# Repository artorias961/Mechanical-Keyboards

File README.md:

# Summary

This project documents the design and iteration of custom mechanical keyboards, covering schematic capture and PCB layout in KiCad, along with firmware and key-mapping experiments. The repository tracks multiple hardware revisions, including an archived AVR-based design and a newer ESP32-S3 implementation exploring wireless connectivity, expanded I/O, and modern MCU capabilities.

The goal is to serve as both a personal learning record and a practical reference for others interested in building custom keyboards from the ground up.

## Lore / Why this exists

Pretty much I’m a keyboard fanatic — I’ve owned ~5 keyboards. During COVID I spent most of my time at home and wanted to learn PCB design. My first version was a huge learning curve, so I’m keeping everything here so others can use it as a reference (or improve it beyond what I could do)

## Keyboard versions

### Version 2 — ESP32-S3-WROOM-1

**Why ESP32-S3:**
- The main seller is **Bluetooth** + **serial pins**.
- ESP32-S3-WROOM-1 is positioned as a flagship ESP chip.
- More computing power, memory, and I/O flexibility than ATMEGA32A-PU 

(You also captured a quick MCU comparison table in the repo notes.) 

| Feature / MCU             | ATmega328P                                 | ATmega32A-PU                | Raspberry Pi Pico (RP2040)                    | ESP32 (e.g., Nano ESP32)                              |
| ------------------------- | ------------------------------------------ | --------------------------- | --------------------------------------------- | ----------------------------------------------------- |
| **Architecture**          | 8-bit AVR                                  | 8-bit AVR                   | 32-bit ARM Cortex-M0+                         | 32-bit Tensilica Xtensa (some variants up to 240 MHz) |
| **Clock Speed**           | ~20 MHz typical                            | ~16 MHz typical             | 133 MHz dual-core                             | Up to ~240 MHz dual-core                              |
| **Flash Memory**          | 32 KB                                      | 32 KB                       | 2 MB (on board)                               | 4 MB+ typical                                         |
| **SRAM**                  | ~2 KB                                      | ~2 KB                       | ~264 KB                                       | ~520 KB+                                              |
| **I/O Pins**              | ~23 I/O                                    | ~32 I/O                     | ~26 GPIO                                      | ~30+ GPIO                                             |
| **Wireless Connectivity** | None                                       | None                        | Default none (Pico); **Pico W has Wi-Fi/BLE** | Wi-Fi & Bluetooth built-in                            |
| **USB Support**           | Needs external interface                   | Needs external interface    | USB device (native)                           | USB & Serial                                          |
| **Power**                 | Low                                        | Low                         | Moderate                                      | Moderate                                              |
| **Ease of Programming**   | Arduino IDE / Atmel Studio                 | Arduino IDE / Atmel Studio  | C/C++, MicroPython                            | Arduino IDE, MicroPython, FreeRTOS                    |
| **Typical Use**           | Simple control, low power, classic Arduino | Similar to 328 with more IO | Faster MCU tasks, multicore                   | IoT, wireless, rich features                          |
| **Price (chip only)**     | ~$2–$3                                     | ~$4–$6                      | ~$3–$6                                        | ~$10–$20                                              |

### Version 1 — ATMEGA32A-PU (Archive)

**Why ATMEGA32A-PU (vs ATMEGA328):**
- Preferred over ATMEGA328 due to **more pins**.
- No dedicated serial pins.
- Enough pins for **LEDs**, an **OLED**, and possibly a Bluetooth module.
- Main concern: **not wireless**.

This version wasn’t manufactured at the time due to a ~$100 quote for a single PCB (around 2021). Here are some pictures from V1:

## Key footprint sizing notes

Standard keyboard size footprints captured in the repo notes: 
- Majority are **1.0U**
- **Seven** 1.25U
- **Two** 1.50U
- **One** 1.75U
- **One** 2.00U
- **Two** 2.25U
- **One** 2.75U
- **One** 6.25U

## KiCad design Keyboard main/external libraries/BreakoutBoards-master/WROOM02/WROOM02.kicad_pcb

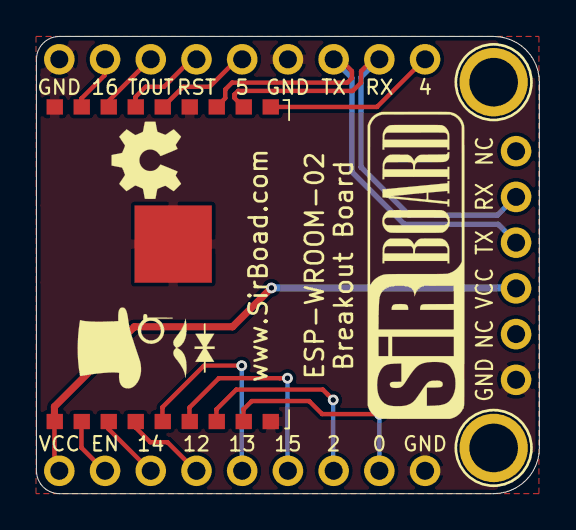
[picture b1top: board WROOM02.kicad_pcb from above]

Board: 2 copper layers, 27.9 x 25.4 mm, 6 parts (0 on the bottom side), 16 nets.

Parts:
H1, H2: MountingHole; MountingHole_M2.5_SirBoard
J1, J2: Conn_01x09; PinHeader_1x09_P2.54mm_Vertical
J3: Conn_01x06; PinHeader_1x06_P2.54mm_Vertical
U1: ESP-WROOM-02

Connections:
EN: J1.2, U1.2
GND: J1.9, J2.1, J2.6, J3.1, U1.9, U1.13, U1.18, U1.19
GPI16: J2.2, U1.17
GPIO0: J1.8, U1.8
GPIO2: J1.7, U1.7
GPIO4: J2.9, U1.10
GPIO5: J2.5, U1.14
GPIO12: J1.4, U1.4
GPIO13: J1.5, U1.5
GPIO14: J1.3, U1.3
GPIO15: J1.6, U1.6
RST: J2.4, U1.15
RXD: J2.8, J3.5, U1.11
TOUT: J2.3, U1.16
TXD: J2.7, J3.4, U1.12
VCC: J1.1, J3.3, U1.1

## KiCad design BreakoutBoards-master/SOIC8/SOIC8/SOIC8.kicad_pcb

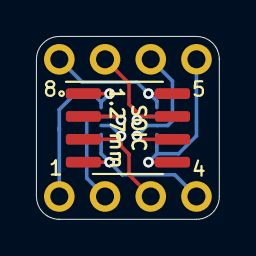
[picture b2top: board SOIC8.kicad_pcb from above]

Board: 2 copper layers, 10.2 x 10.2 mm, 4 parts (1 on the bottom side), 8 nets.

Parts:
J1, J2: Conn_01x04; PinHeader_1x04_P2.54mm_Vertical
J3: SOIC8; SOIC-8_3.9x4.9mm_P1.27mm
J4: VSSOP8; VSSOP-8_2.3x2mm_P0.5mm

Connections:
unnamed: J1.1, J3.8, J4.1
unnamed: J1.2, J3.7, J4.2
unnamed: J1.3, J3.6, J4.3
unnamed: J1.4, J3.5, J4.4
unnamed: J2.1, J3.1, J4.8
unnamed: J2.2, J3.2, J4.7
unnamed: J2.3, J3.3, J4.6
unnamed: J2.4, J3.4, J4.5

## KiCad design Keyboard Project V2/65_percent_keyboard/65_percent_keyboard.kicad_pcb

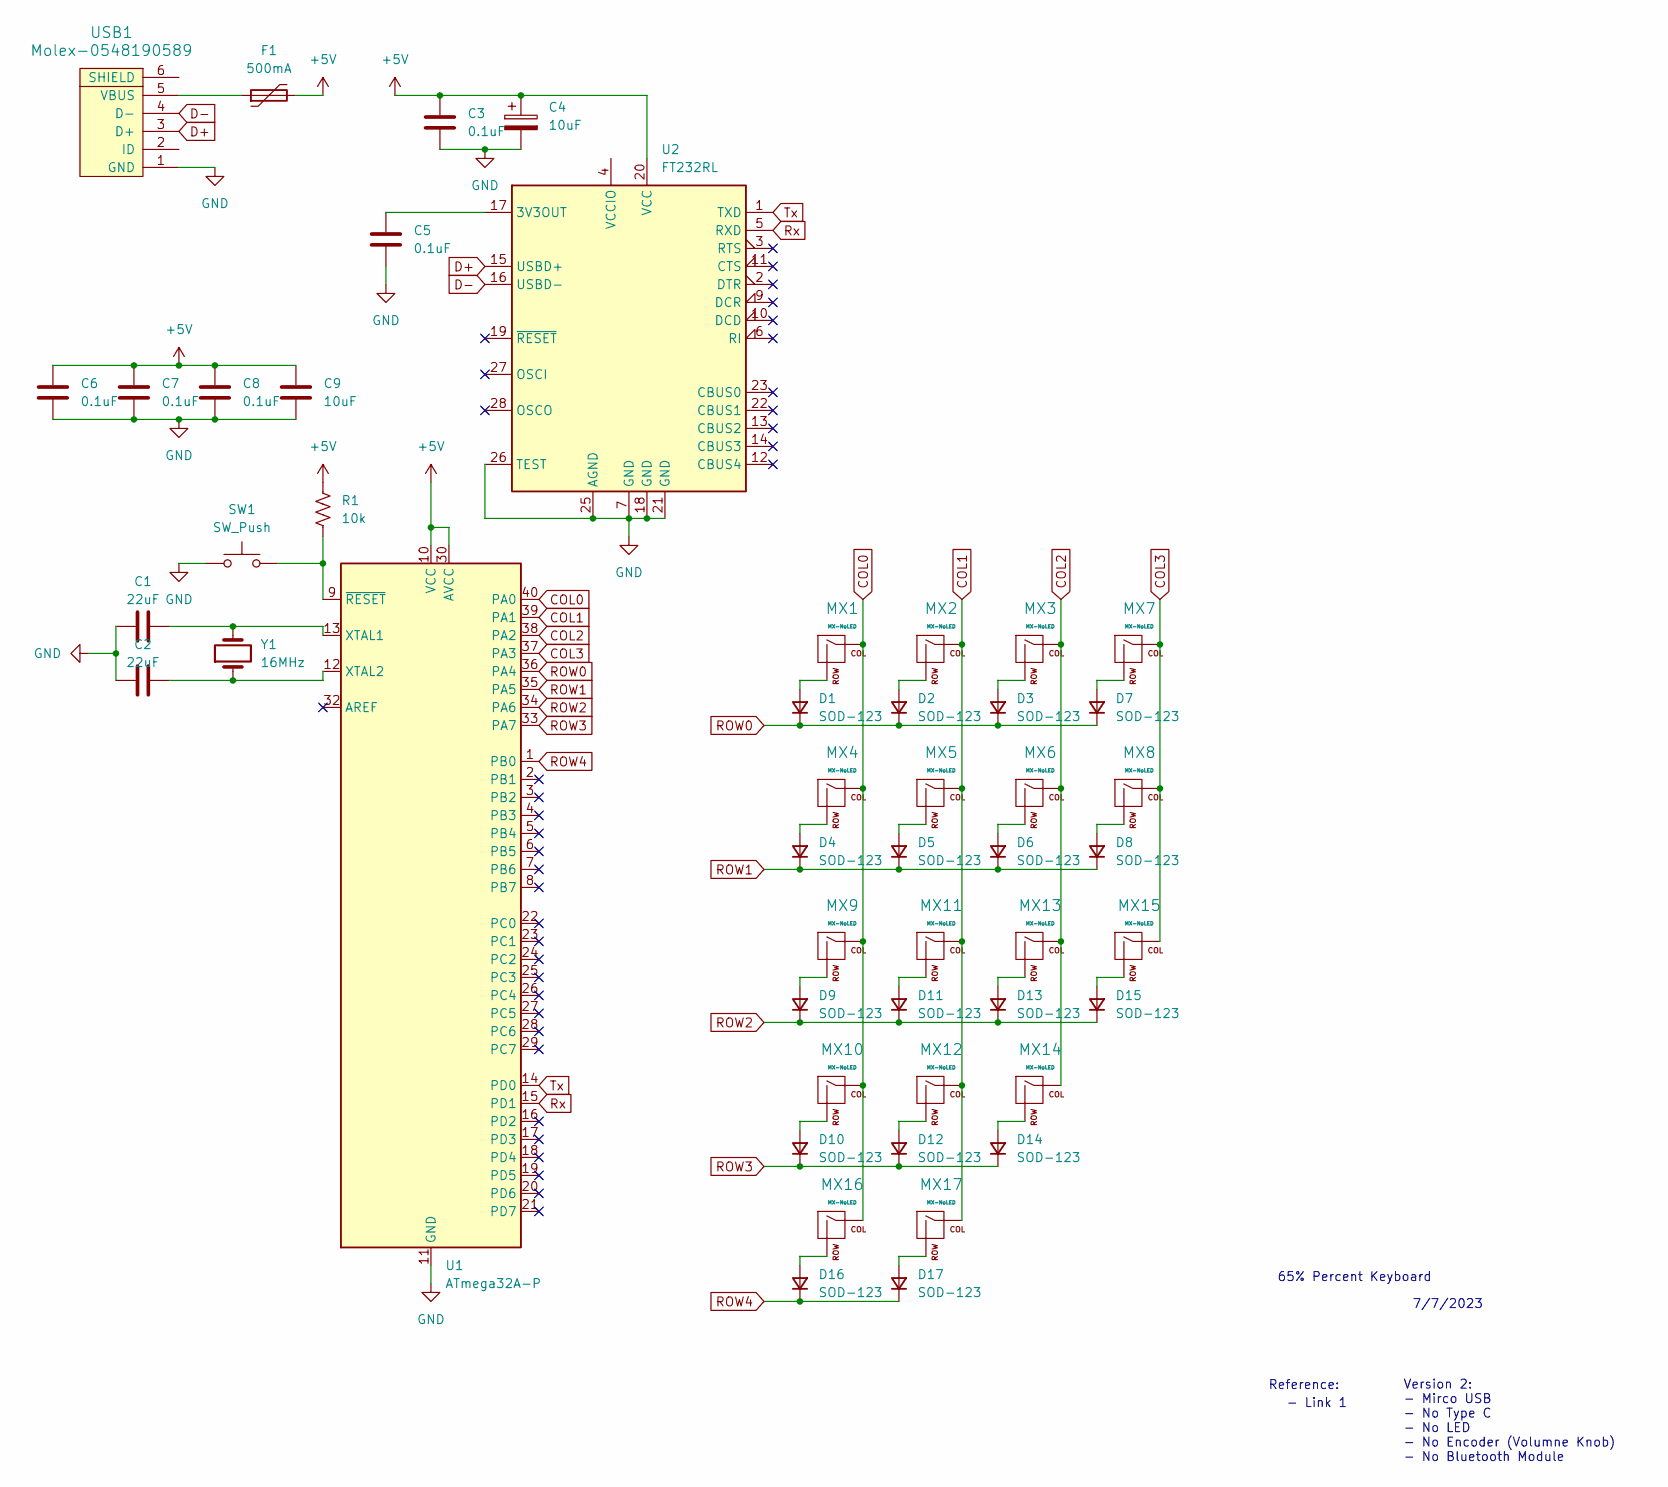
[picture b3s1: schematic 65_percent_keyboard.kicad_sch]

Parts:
C1, C2: 22uF; C_0805_2012Metric
C3, C5, C6, C7, C8: 0.1uF; C_0805_2012Metric
C4, C9: 10uF; C_0805_2012Metric
D1, D2, D3, D4, D5, D6, D7, D8, D9, D10, D11, D12, D13, D14, D15, D16, D17: SOD-123; D_SOD-123
F1: 500mA; Fuse_1206_3216Metric
MX1, MX2, MX3, MX4, MX5, MX6, MX7, MX8, MX9, MX10, MX11, MX12, MX13, MX14, MX15, MX16, MX17: MX-NoLED; MX-1U-NoLED
R1: 10k; R_0805_2012Metric
SW1: SW_Push; SKQG-1155865
U1: ATmega32A-P; DIP-40_W15.24mm
U2: FT232RL; SSOP-28_5.3x10.2mm_P0.65mm
USB1: Molex-0548190589
Y1: 16MHz; Crystal_SMD_3225-4Pin_3.2x2.5mm

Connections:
+5V: C3.1, C4.1, C6.1, C7.1, C8.1, C9.1, F1.2, R1.2, U1.10 (VCC), U1.30 (AVCC), U2.20 (VCC)
COL0: MX1.1 (COL), MX4.1 (COL), MX9.1 (COL), MX10.1 (COL), MX16.1 (COL), U1.40 (PA0)
COL1: MX2.1 (COL), MX5.1 (COL), MX11.1 (COL), MX12.1 (COL), MX17.1 (COL), U1.39 (PA1)
COL2: MX3.1 (COL), MX6.1 (COL), MX13.1 (COL), MX14.1 (COL), U1.38 (PA2)
COL3: MX7.1 (COL), MX8.1 (COL), MX15.1 (COL), U1.37 (PA3)
D+: U2.15 (USBD+), USB1.3 (D+)
D-: U2.16 (USBD-), USB1.4 (D-)
GND: C1.1, C2.1, C3.2, C4.2, C5.2, C6.2, C7.2, C8.2, C9.2, SW1.1, U1.11 (GND), U1.31 (GND), U2.7 (GND), U2.18 (GND), U2.21 (GND), U2.25 (AGND), U2.26 (TEST), USB1.1 (GND)
unnamed: D1.2 (A), MX1.2 (ROW)
unnamed: D2.2 (A), MX2.2 (ROW)
unnamed: D3.2 (A), MX3.2 (ROW)
unnamed: D4.2 (A), MX4.2 (ROW)
unnamed: D5.2 (A), MX5.2 (ROW)
unnamed: D6.2 (A), MX6.2 (ROW)
unnamed: D7.2 (A), MX7.2 (ROW)
unnamed: D8.2 (A), MX8.2 (ROW)
unnamed: D9.2 (A), MX9.2 (ROW)
unnamed: D10.2 (A), MX10.2 (ROW)
unnamed: D11.2 (A), MX11.2 (ROW)
unnamed: D12.2 (A), MX12.2 (ROW)
unnamed: D13.2 (A), MX13.2 (ROW)
unnamed: D14.2 (A), MX14.2 (ROW)
unnamed: D15.2 (A), MX15.2 (ROW)
unnamed: D16.2 (A), MX16.2 (ROW)
unnamed: D17.2 (A), MX17.2 (ROW)
unnamed: C1.2, U1.13 (XTAL1), Y1.2
unnamed: C2.2, U1.12 (XTAL2), Y1.1
unnamed: R1.1, SW1.2, U1.9 (~RESET)
unnamed: C5.1, U2.17 (3V3OUT)
unnamed: F1.1, USB1.5 (VBUS)
ROW0: D1.1 (K), D2.1 (K), D3.1 (K), D7.1 (K), U1.36 (PA4)
ROW1: D4.1 (K), D5.1 (K), D6.1 (K), D8.1 (K), U1.35 (PA5)
ROW2: D9.1 (K), D11.1 (K), D13.1 (K), D15.1 (K), U1.34 (PA6)
ROW3: D10.1 (K), D12.1 (K), D14.1 (K), U1.33 (PA7)
ROW4: D16.1 (K), D17.1 (K), U1.1 (PB0)
Rx: U1.15 (PD1), U2.5 (RXD)
Tx: U1.14 (PD0), U2.1 (TXD)

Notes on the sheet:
Version 2: - Mirco USB - No Type C - No LED - No Encoder (Volumne Knob) - No Bluetooth Module
65% Percent Keyboard
7/7/2023
- Link 1
Reference:

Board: 2 copper layers, 50 parts (0 on the bottom side), 37 nets, no tracks yet.

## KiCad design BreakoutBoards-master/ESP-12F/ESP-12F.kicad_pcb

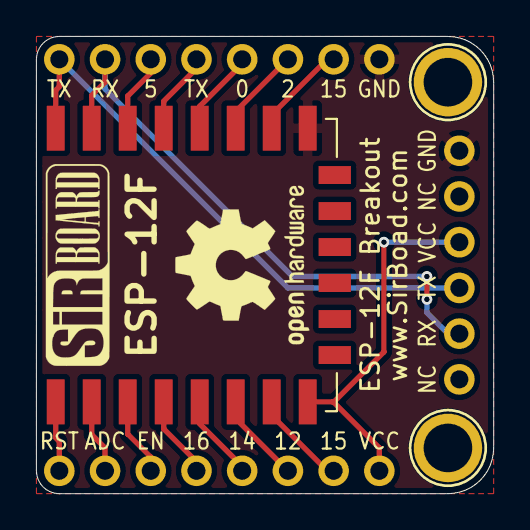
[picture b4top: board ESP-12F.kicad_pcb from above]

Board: 2 copper layers, 25.4 x 25.4 mm, 6 parts (0 on the bottom side), 16 nets.

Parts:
ESP-12F: ESP-12F; ESP-12E
H2, H4: MountingHole; MountingHole_M2.5_SirBoard
J1, J2: Conn_01x08; PinHeader_1x08_P2.54mm_Vertical
J3: Conn_01x06; PinHeader_1x06_P2.54mm_Horizontal

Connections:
ADC: ESP-12F.2, J1.2
EN: ESP-12F.3, J1.3
GND: ESP-12F.15, J2.8, J3.1
GPI16: ESP-12F.4, J1.4
GPIO0: ESP-12F.18, J2.5
GPIO2: ESP-12F.17, J2.6
GPIO4: ESP-12F.19, J2.4
GPIO5: ESP-12F.20, J2.3
GPIO12: ESP-12F.6, J1.6
GPIO13: ESP-12F.7, J1.7
GPIO14: ESP-12F.5, J1.5
GPIO15: ESP-12F.16, J2.7
RST: ESP-12F.1, J1.1
RX: ESP-12F.21, J2.2, J3.5
TXD: ESP-12F.22, J2.1, J3.4
VCC: ESP-12F.8, J1.8, J3.3

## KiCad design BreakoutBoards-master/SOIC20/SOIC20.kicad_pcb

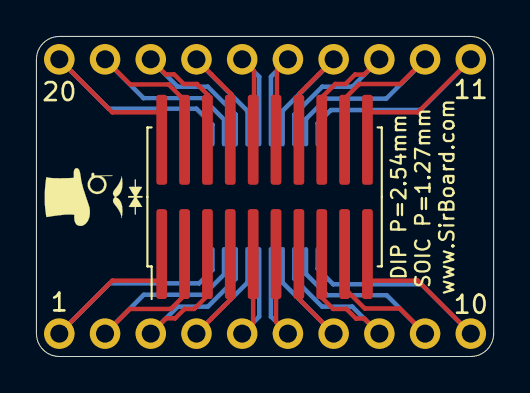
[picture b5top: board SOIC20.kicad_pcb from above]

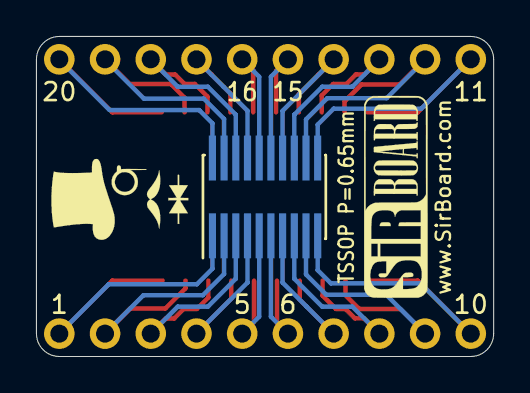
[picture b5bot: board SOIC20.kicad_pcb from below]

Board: 2 copper layers, 25.4 x 17.8 mm, 4 parts (3 on the bottom side), 20 nets.

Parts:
J1, J5: Conn_01x10; PinHeader_1x10_P2.54mm_Vertical
J2: Conn_02x10_Counter_Clockwise; SOIC-20W_7.5x12.8mm_P1.27mm
J4: Conn_02x10_Counter_Clockwise; SSOP-20_4.4x6.5mm_P0.65mm

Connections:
unnamed: J1.1, J2.1, J4.10
unnamed: J1.2, J2.2, J4.9
unnamed: J1.3, J2.3, J4.8
unnamed: J1.4, J2.4, J4.7
unnamed: J1.5, J2.5, J4.6
unnamed: J1.6, J2.6, J4.5
unnamed: J1.7, J2.7, J4.4
unnamed: J1.8, J2.8, J4.3
unnamed: J1.9, J2.9, J4.2
unnamed: J1.10, J2.10, J4.1
unnamed: J2.11, J4.20, J5.1
unnamed: J2.12, J4.19, J5.2
unnamed: J2.13, J4.18, J5.3
unnamed: J2.14, J4.17, J5.4
unnamed: J2.15, J4.16, J5.5
unnamed: J2.16, J4.15, J5.6
unnamed: J2.17, J4.14, J5.7
unnamed: J2.18, J4.13, J5.8
unnamed: J2.19, J4.12, J5.9
unnamed: J2.20, J4.11, J5.10

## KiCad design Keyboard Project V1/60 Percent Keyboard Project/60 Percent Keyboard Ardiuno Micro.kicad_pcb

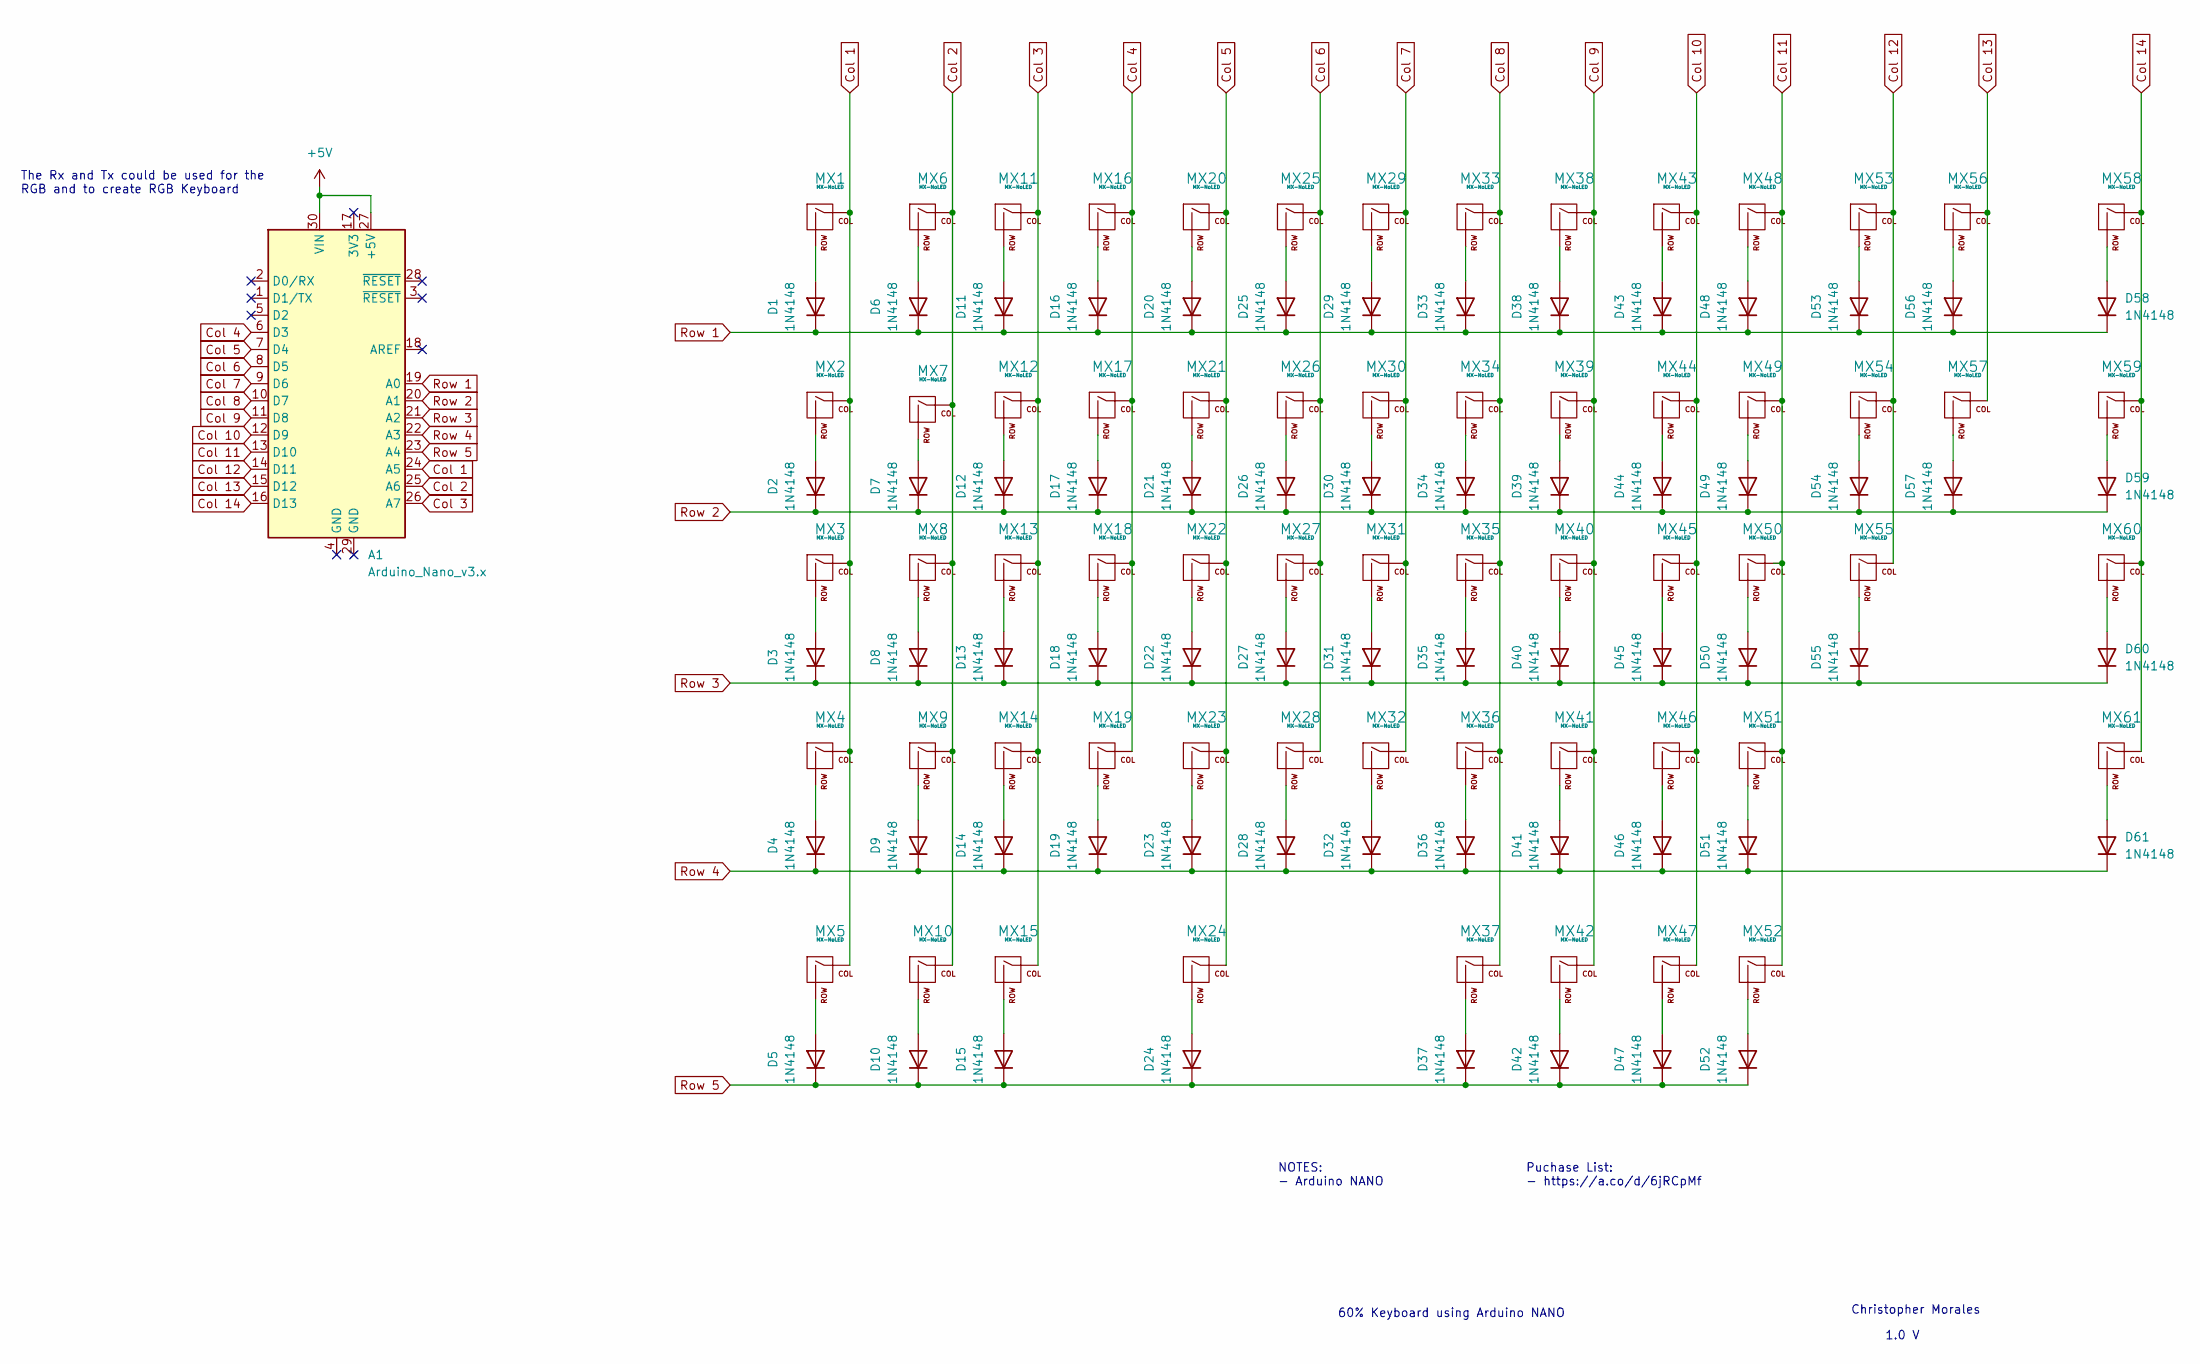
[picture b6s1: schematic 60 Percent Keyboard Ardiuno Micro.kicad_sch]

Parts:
A1: Arduino_Nano_v3.x; Arduino_Nano
D1, D2, D3, D4, D5, D6, D7, D8, D9, D10, D11, D12, D13, D14, D15, D16, D17, D18, D19, D20, D21, D22, D23, D24, D25, D26, D27, D28, D29, D30, D31, D32, D33, D34, D35, D36, D37, D38, D39, D40, D41, D42, D43, D44, D45, D46, D47, D48, D49, D50, D51, D52, D53, D54, D55, D56, D57, D58, D59, D60, D61: 1N4148; D_DO-35_SOD27_P7.62mm_Horizontal
MX1, MX6, MX7, MX8, MX9, MX11, MX12, MX13, MX14, MX16, MX17, MX18, MX19, MX20, MX21, MX22, MX23, MX25, MX26, MX27, MX28, MX29, MX30, MX31, MX32, MX33, MX34, MX35, MX36, MX38, MX39, MX40, MX41, MX43, MX44, MX45, MX46, MX48, MX49, MX50, MX51, MX53, MX54, MX55, MX56, MX57: MX-NoLED; SW_Cherry_MX_PCB_1.00u
MX2, MX59: MX-NoLED; SW_Cherry_MX_PCB_1.50u
MX3: MX-NoLED; SW_Cherry_MX_PCB_1.75u
MX4, MX60: MX-NoLED; SW_Cherry_MX_PCB_2.25u
MX5, MX10, MX15, MX37, MX42, MX47, MX52: MX-NoLED; SW_Cherry_MX_PCB_1.25u
MX24: MX-NoLED; SW_Cherry_MX_PCB_6.25u
MX58: MX-NoLED; SW_Cherry_MX_PCB_2.00u
MX61: MX-NoLED; SW_Cherry_MX_PCB_2.75u

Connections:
Col 1: A1.24 (A5), MX1.1 (COL), MX2.1 (COL), MX3.1 (COL), MX4.1 (COL), MX5.1 (COL)
Col 2: A1.25 (A6), MX6.1 (COL), MX7.1 (COL), MX8.1 (COL), MX9.1 (COL), MX10.1 (COL)
Col 3: A1.26 (A7), MX11.1 (COL), MX12.1 (COL), MX13.1 (COL), MX14.1 (COL), MX15.1 (COL)
Col 4: A1.6 (D3), MX16.1 (COL), MX17.1 (COL), MX18.1 (COL), MX19.1 (COL)
Col 5: A1.7 (D4), MX20.1 (COL), MX21.1 (COL), MX22.1 (COL), MX23.1 (COL), MX24.1 (COL)
Col 6: A1.8 (D5), MX25.1 (COL), MX26.1 (COL), MX27.1 (COL), MX28.1 (COL)
Col 7: A1.9 (D6), MX29.1 (COL), MX30.1 (COL), MX31.1 (COL), MX32.1 (COL)
Col 8: A1.10 (D7), MX33.1 (COL), MX34.1 (COL), MX35.1 (COL), MX36.1 (COL), MX37.1 (COL)
Col 9: A1.11 (D8), MX38.1 (COL), MX39.1 (COL), MX40.1 (COL), MX41.1 (COL), MX42.1 (COL)
Col 10: A1.12 (D9), MX43.1 (COL), MX44.1 (COL), MX45.1 (COL), MX46.1 (COL), MX47.1 (COL)
Col 11: A1.13 (D10), MX48.1 (COL), MX49.1 (COL), MX50.1 (COL), MX51.1 (COL), MX52.1 (COL)
Col 12: A1.14 (D11), MX53.1 (COL), MX54.1 (COL), MX55.1 (COL)
Col 13: A1.15 (D12), MX56.1 (COL), MX57.1 (COL)
Col 14: A1.16 (D13), MX58.1 (COL), MX59.1 (COL), MX60.1 (COL), MX61.1 (COL)
unnamed: D1.2 (A), MX1.2 (ROW)
unnamed: D2.2 (A), MX2.2 (ROW)
unnamed: D3.2 (A), MX3.2 (ROW)
unnamed: D4.2 (A), MX4.2 (ROW)
unnamed: D5.2 (A), MX5.2 (ROW)
unnamed: D6.2 (A), MX6.2 (ROW)
unnamed: D7.2 (A), MX7.2 (ROW)
unnamed: D8.2 (A), MX8.2 (ROW)
unnamed: D9.2 (A), MX9.2 (ROW)
unnamed: D10.2 (A), MX10.2 (ROW)
unnamed: D11.2 (A), MX11.2 (ROW)
unnamed: D12.2 (A), MX12.2 (ROW)
unnamed: D13.2 (A), MX13.2 (ROW)
unnamed: D14.2 (A), MX14.2 (ROW)
unnamed: D15.2 (A), MX15.2 (ROW)
unnamed: D16.2 (A), MX16.2 (ROW)
unnamed: D17.2 (A), MX17.2 (ROW)
unnamed: D18.2 (A), MX18.2 (ROW)
unnamed: D19.2 (A), MX19.2 (ROW)
unnamed: D20.2 (A), MX20.2 (ROW)
unnamed: D21.2 (A), MX21.2 (ROW)
unnamed: D22.2 (A), MX22.2 (ROW)
unnamed: D23.2 (A), MX23.2 (ROW)
unnamed: D24.2 (A), MX24.2 (ROW)
unnamed: D25.2 (A), MX25.2 (ROW)
unnamed: D26.2 (A), MX26.2 (ROW)
unnamed: D27.2 (A), MX27.2 (ROW)
unnamed: D28.2 (A), MX28.2 (ROW)
unnamed: D29.2 (A), MX29.2 (ROW)
unnamed: D30.2 (A), MX30.2 (ROW)
unnamed: D31.2 (A), MX31.2 (ROW)
unnamed: D32.2 (A), MX32.2 (ROW)
unnamed: D33.2 (A), MX33.2 (ROW)
unnamed: D34.2 (A), MX34.2 (ROW)
unnamed: D35.2 (A), MX35.2 (ROW)
unnamed: D36.2 (A), MX36.2 (ROW)
unnamed: D37.2 (A), MX37.2 (ROW)
unnamed: D38.2 (A), MX38.2 (ROW)
unnamed: D39.2 (A), MX39.2 (ROW)
unnamed: D40.2 (A), MX40.2 (ROW)
unnamed: D41.2 (A), MX41.2 (ROW)
unnamed: D42.2 (A), MX42.2 (ROW)
unnamed: D43.2 (A), MX43.2 (ROW)
unnamed: D44.2 (A), MX44.2 (ROW)
unnamed: D45.2 (A), MX45.2 (ROW)
unnamed: D46.2 (A), MX46.2 (ROW)
unnamed: D47.2 (A), MX47.2 (ROW)
unnamed: D48.2 (A), MX48.2 (ROW)
unnamed: D49.2 (A), MX49.2 (ROW)
unnamed: D50.2 (A), MX50.2 (ROW)
unnamed: D51.2 (A), MX51.2 (ROW)
unnamed: D52.2 (A), MX52.2 (ROW)
unnamed: D53.2 (A), MX53.2 (ROW)
unnamed: D54.2 (A), MX54.2 (ROW)
unnamed: D55.2 (A), MX55.2 (ROW)
unnamed: D56.2 (A), MX56.2 (ROW)
unnamed: D57.2 (A), MX57.2 (ROW)
unnamed: D58.2 (A), MX58.2 (ROW)
unnamed: D59.2 (A), MX59.2 (ROW)
unnamed: D60.2 (A), MX60.2 (ROW)
unnamed: D61.2 (A), MX61.2 (ROW)
Row 1: A1.19 (A0), D1.1 (K), D6.1 (K), D11.1 (K), D16.1 (K), D20.1 (K), D25.1 (K), D29.1 (K), D33.1 (K), D38.1 (K), D43.1 (K), D48.1 (K), D53.1 (K), D56.1 (K), D58.1 (K)
Row 2: A1.20 (A1), D2.1 (K), D7.1 (K), D12.1 (K), D17.1 (K), D21.1 (K), D26.1 (K), D30.1 (K), D34.1 (K), D39.1 (K), D44.1 (K), D49.1 (K), D54.1 (K), D57.1 (K), D59.1 (K)
Row 3: A1.21 (A2), D3.1 (K), D8.1 (K), D13.1 (K), D18.1 (K), D22.1 (K), D27.1 (K), D31.1 (K), D35.1 (K), D40.1 (K), D45.1 (K), D50.1 (K), D55.1 (K), D60.1 (K)
Row 4: A1.22 (A3), D4.1 (K), D9.1 (K), D14.1 (K), D19.1 (K), D23.1 (K), D28.1 (K), D32.1 (K), D36.1 (K), D41.1 (K), D46.1 (K), D51.1 (K), D61.1 (K)
Row 5: A1.23 (A4), D5.1 (K), D10.1 (K), D15.1 (K), D24.1 (K), D37.1 (K), D42.1 (K), D47.1 (K), D52.1 (K)

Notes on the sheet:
1.0 V
The Rx and Tx could be used for the RGB and to create RGB Keyboard
Puchase List: - https://a.co/d/6jRCpMf
Christopher Morales
60% Keyboard using Arduino NANO
NOTES: - Arduino NANO

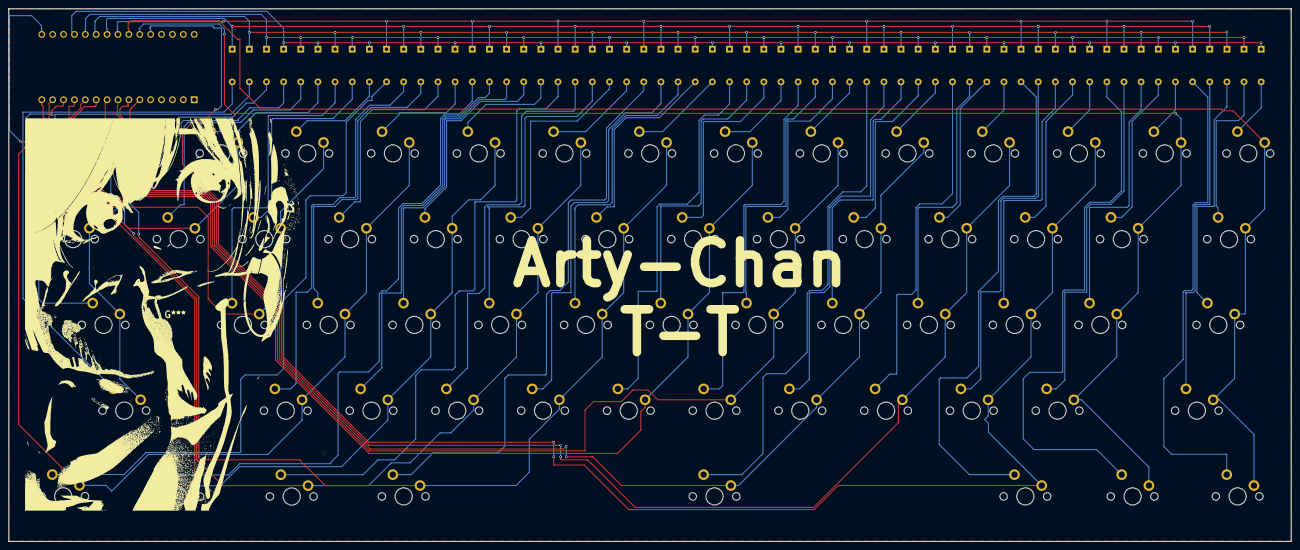
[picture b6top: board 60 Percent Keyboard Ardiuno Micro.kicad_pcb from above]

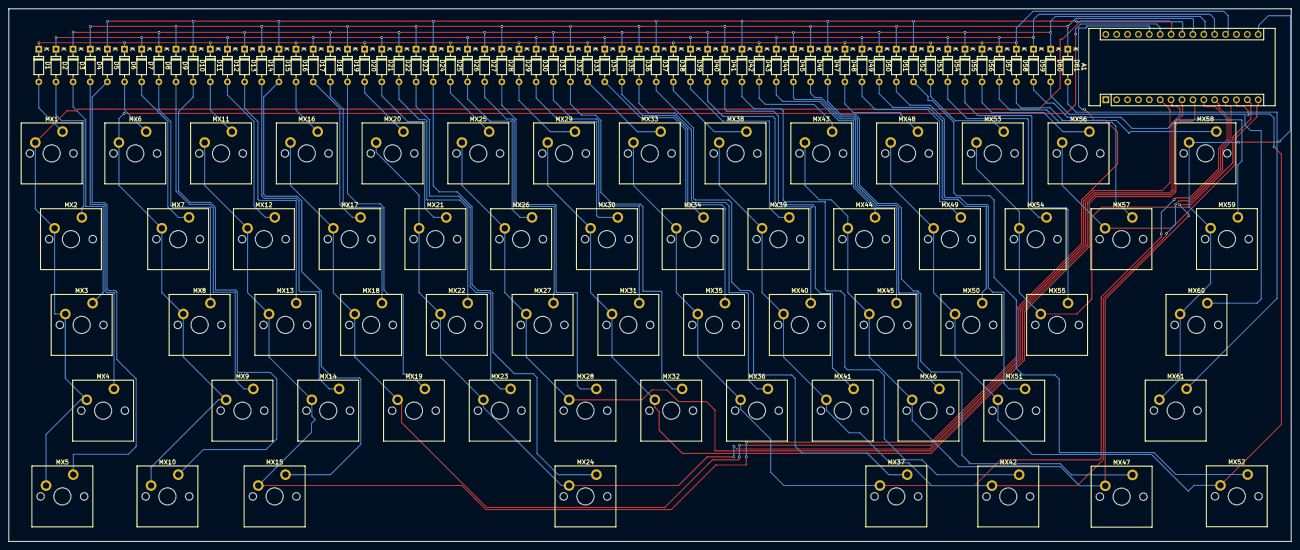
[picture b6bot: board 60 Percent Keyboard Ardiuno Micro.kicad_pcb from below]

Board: 2 copper layers, 299.1 x 124.2 mm, 123 parts (123 on the bottom side), 80 nets.

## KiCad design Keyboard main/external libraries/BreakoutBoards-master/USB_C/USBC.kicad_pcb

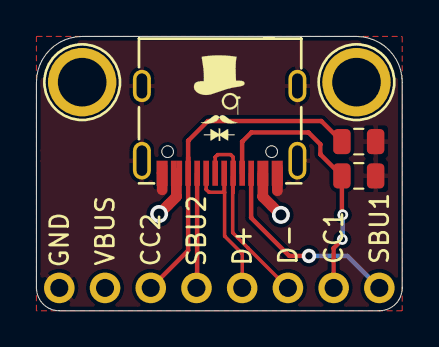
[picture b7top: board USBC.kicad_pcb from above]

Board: 2 copper layers, 20.3 x 15.2 mm, 6 parts (0 on the bottom side), 8 nets.

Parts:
H1, H2: MountingHole; MountingHole_M2.5_SirBoard
J1: USB_C_Receptacle_USB2.0; USB_C
J2: Conn_01x08; PinHeader_1x08_P2.54mm_Vertical
R1, R2: 5K1; R_0805_2012Metric

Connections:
/CC1: J1.A5, J2.7, R1.2
/CC2: J1.B5, J2.3, R2.2
/D+: J1.A6, J1.B6, J2.5
/D-: J1.A7, J1.B7, J2.6
/SBU1: J1.A8, J2.4
/SBU2: J1.B8, J2.8
/VBUS: J1.A4, J1.A9, J1.B4, J1.B9, J2.2
GND: J1.A1, J1.A12, J1.B1, J1.B12, J1.S1, J2.1, R1.1, R2.1

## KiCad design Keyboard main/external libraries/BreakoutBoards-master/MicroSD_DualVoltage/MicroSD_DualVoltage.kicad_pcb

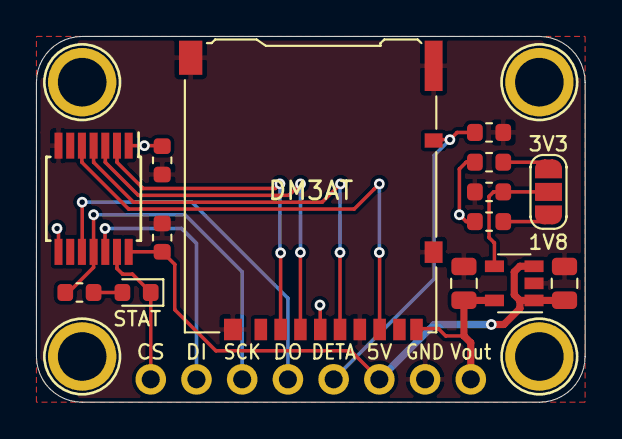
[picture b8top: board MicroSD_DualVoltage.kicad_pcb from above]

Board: 2 copper layers, 30.5 x 20.3 mm, 19 parts (1 on the bottom side), 16 nets.

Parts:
C1, C2: 10uF; C_0805_2012Metric
C3, C4: 100nF; C_0603_1608Metric
DM3AT: Micro_SD_Card_Det; microSD_HC_Hirose_DM3AT-SF-PEJM5
H1, H2, H3, H4: MountingHole; MountingHole_M2.5_SirBoard
J1: Conn_01x08; PinHeader_1x08_P2.54mm_Vertical
JP1: SolderJumper_3_Open; SolderJumper-3_P1.3mm_Open_RoundedPad1.0x1.5mm
R1: 31K6; R_0603_1608Metric
R2: 12K4; R_0603_1608Metric
R3, R4: 10K; R_0603_1608Metric
R6: 1K; R_0603_1608Metric
STAT: LED; LED_0603_1608Metric
U1: AP7365; SOT-23-5
U2: TXB0104PW; TSSOP-14_4.4x5mm_P0.65mm

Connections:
/CLK_SD: DM3AT.5, U2.4
/CS_SD: DM3AT.2, U2.2
/DI_SD: DM3AT.3, U2.3
/DO_SD: DM3AT.7, U2.5
ADJ: JP1.2, R3.1, U1.4
CS: J1.1, STAT.1, U2.13
DETA: DM3AT.10, J1.5, R4.1
DI: J1.2, U2.12
DO: J1.4, U2.10
GND: C1.2, C2.2, C3.2, C4.2, DM3AT.6, DM3AT.11, J1.7, R3.2, R4.2, U1.2, U2.7
unnamed: R6.2, STAT.2
unnamed: JP1.1, R1.2
unnamed: JP1.3, R2.2
SCK: J1.3, R6.1, U2.11
VIN: C1.1, C3.1, J1.6, U1.1, U1.3, U2.14
VOUT: C2.1, C4.1, DM3AT.4, DM3AT.9, J1.8, R1.1, R2.1, U1.5, U2.1, U2.8

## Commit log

2022-09-04 This is my first commit and journey of creating a keyboard using arduino chips for now :D
2022-09-04 Create README.md for mechanical keyboards :D
    Adding description about the plans of the future and what i have currently
2022-09-04 Im using the Arduino NANO not Pro Micro
    Made an error, Im using the arduino nano not the arduino pro micro
2022-09-05 Sizes of each keycap size
2022-09-06 updated version of version 1 and currently in the PCB editor. Almost done with version one and may work on version V1.1 after this
2022-09-06 Finally completed 1 versiongit add .!
2022-09-06 Version 1 is completed with the gerber files
2022-12-31 adding
2023-02-10 update info
2023-05-01 updating directory
2023-07-08 cleaning directory
2023-07-08 schematics for version 2
2023-07-09 updated directory
2023-07-09 updated keyboard project 2, just need to add the switches and minor tweaks
2023-07-09 fixed the Rx/Tx wire
2023-07-31 fixed most of the components
2023-08-06 updated and fixed keyboard
2025-11-04 backup
2025-11-10 added keyboard sheet
2025-11-10 added kicad library
2025-12-24 cleaning directory more
2025-12-24 updating
2025-12-24 updating README with version comparisons and images
    Added detailed comparisons and features for ESP32-S3-WROOM-1 and ATMEGA32A-PU. Included images and additional notes on the versions.
2025-12-24 making it a bit readme better
2025-12-24 forgot to erase something
